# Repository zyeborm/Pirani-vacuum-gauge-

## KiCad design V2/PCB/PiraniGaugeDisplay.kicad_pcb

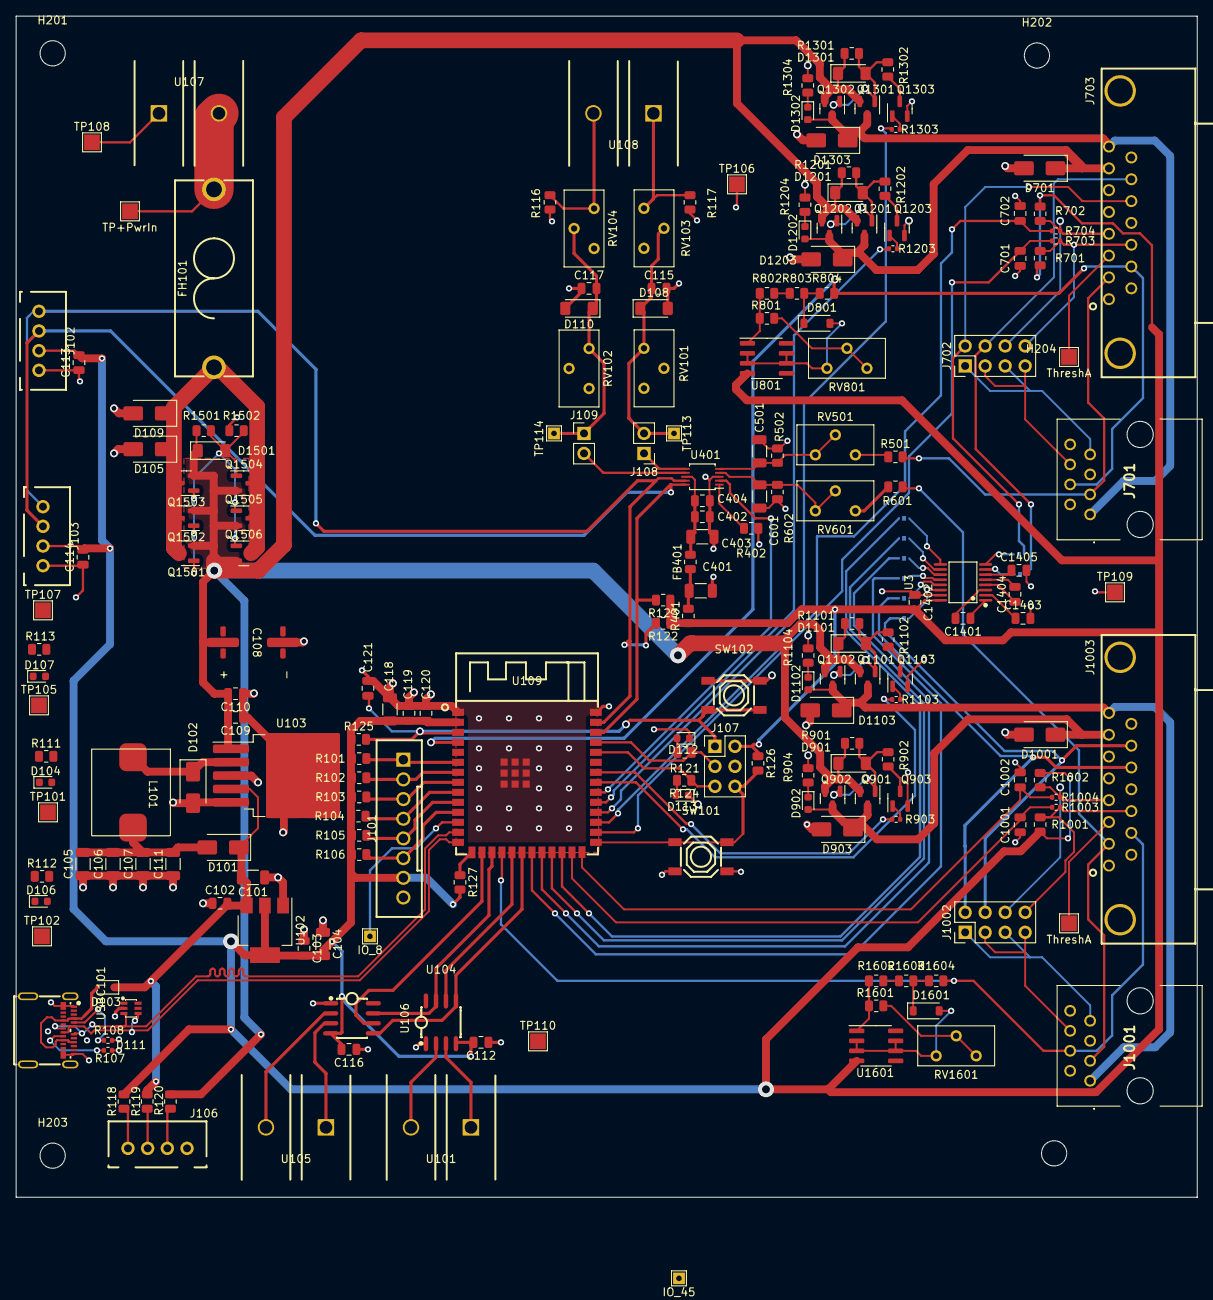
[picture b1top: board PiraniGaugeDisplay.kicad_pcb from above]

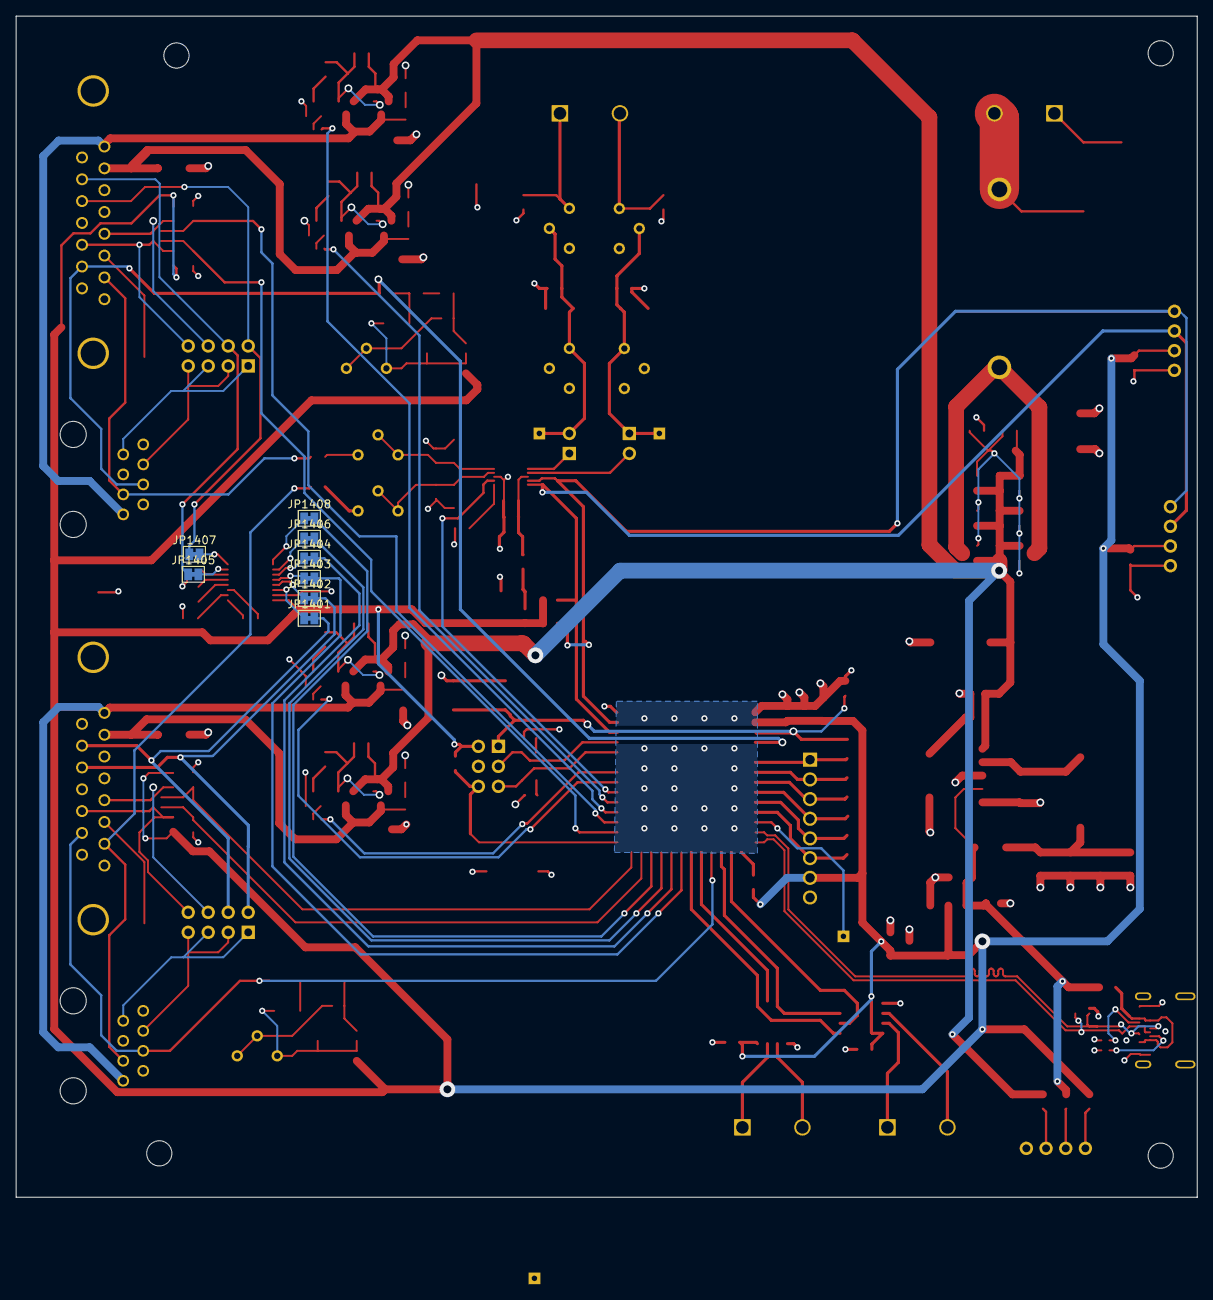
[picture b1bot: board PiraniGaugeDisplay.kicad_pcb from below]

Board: 4 copper layers, 150.0 x 150.0 mm, 214 parts (8 on the bottom side), 132 nets.

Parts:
C101, C104, C105, C106, C107, C111, C118, C402: 47uF; C_1206_3216Metric
C102, C103, C110, C112, C113, C114, C116, C120, C404, C1401, C1403, C1404, C1405: 100nf; C_0805_2012Metric
C108: 220uF; VF_C_Panasonic_ZA_SizeG_VibrationProof
C109, C115, C117, C119, C121, C403, C701, C702, C1001, C1002, C1402: 1uf; C_0805_2012Metric
C401, C501, C601: 10uF; C_1206_3216Metric
D101, D102, D109, D903, D1103, D1203, D1303: SS54; D_SMA
D103: 1N5819WS; D_SOD-323
D104, D106, D107, D112, D113, D902, D1102, D1202, D1302: LED; LED_0603_1608Metric
D105, D701, D1001: SMAJ30CA; D_SMA
D108, D110: ZMM3V3-M; D_MiniMELF
D111: SMF05CT1G; SOT-363_L2.0-W1.3-P0.65-LS2.1-BR
D801, D1601: 1N4148W; D_SOD-123
D901, D1101, D1201, D1301, D1501: ZMM5V6-M; D_MiniMELF
FB401: 300m; R_0805_2012Metric
FH101: FH1-200CK-B; FUSE-TH_L24.8-W9.8-P22.60
H201, H202, H203, H204: MountingHole; MountingHole_3.2mm_M3
J101: B8B-XH-A (LF)(SN); CONN-TH_B8B-XH-A-LF-SN
J102, J103, J106: Conn_01x04; CONN-TH_B4B-XH-A-LF-SN
J107: Conn_02x03_Odd_Even; PinHeader_2x03_P2.54mm_Vertical
J108: Aux1_Iso; PinHeader_1x02_P2.54mm_Vertical
J109: Aux2_Iso; PinHeader_1x02_P2.54mm_Vertical
J701, J1001: RJ45; 55551621
J702, J1002: Conn_02x04_Counter_Clockwise; PinHeader_2x04_P2.54mm_Vertical
J703, J1003: DA15_Plug; DSUB-TH_Z-SUBDRBM602A002
JP1401, JP1402, JP1403, JP1404, JP1405, JP1406, JP1407, JP1408: Jumper_2_Bridged; SolderJumper-2_P1.3mm_Bridged_Pad1.0x1.5mm
L101: 47uH; VF_L_MDA_1040
Q901, Q902, Q1101, Q1102, Q1201, Q1202, Q1301, Q1302, Q1501, Q1502, Q1503, Q1504, Q1505, Q1506: AO3401A; SOT-23
Q903, Q1103, Q1203, Q1303: AO3400A; SOT-23
R101, R102, R103, R104, R105, R106, R111, R112, R118, R119, R121, R122, R123, R124, R402, R701, R702, R1001, R1002: 4K7; R_0805_2012Metric
R107, R108: 5K6; R_0402_1005Metric
R113, R116, R117, R120, R125, R501, R601, R902, R904, R1102, R1104, R1202, R1204, R1302, R1304, R1502: 10K; R_0805_2012Metric
R126, R801, R1601: 3K; R_0805_2012Metric
R127: 100K; R_0805_2012Metric
R401: 10R; R_0805_2012Metric
R502, R602: 2K7; R_0805_2012Metric
R703, R704, R1003, R1004: 4k7; R_0402_1005Metric
R802, R1602: 33K; R_0805_2012Metric
R803, R1603: 1K2; R_0805_2012Metric
R804, R1604: 1K; R_0805_2012Metric
R901, R1101, R1201, R1301, R1501: 3K6; R_0805_2012Metric
R903, R1103, R1203, R1303: 1K; R_0402_1005Metric
RV101, RV102, RV103, RV104, RV501, RV601, RV801, RV1601: 1K; Potentiometer_Bourns_3296Y_Vertical
SW101, SW102: TS-1187A-B-A-B; SW-SMD_4P-L5.1-W5.1-P3.70-LS6.5-TL-2
TP101: TP+5v; TestPoint_Pad_2.0x2.0mm
TP102: TP+3.3; TestPoint_Pad_2.0x2.0mm
TP103: TP+PwrIn; TestPoint_Pad_2.0x2.0mm
TP104: IO_45; TestPoint_THTPad_1.5x1.5mm_Drill0.7mm
TP105: TP+24; TestPoint_Pad_2.0x2.0mm
TP106: TP_GND; TestPoint_Pad_2.0x2.0mm
TP107, TP108, TP109, TP110: SW_GND; TestPoint_Pad_2.0x2.0mm
TP112: IO_8; TestPoint_THTPad_1.5x1.5mm_Drill0.7mm
TP113: TP_Aux1; TestPoint_THTPad_1.5x1.5mm_Drill0.7mm
TP114: TP_Aux2; TestPoint_THTPad_1.5x1.5mm_Drill0.7mm
TP701, TP1001: ThreshA; TestPoint_Pad_2.0x2.0mm
U3: SP3232EEY-L/TR; TSSOP-16_L5.0-W4.4-P0.65-LS6.4-BL
U101, U105, U107, U108: MX25C-7.62-BK01-02P-CU-S-A; CONN-TH_2P-P7.62_MAX_MX25C-7.62-BK01-02P-CU-S-A
U102: AMS1117-3.3; SOT-223-3_TabPin2
U103: LM2596S-5; TO-263-5_TabPin3
U104, U106: MAX6675ISA+T; SOIC-8_L5.0-W4.0-P1.27-LS6.0-BL
U109: ESP32-S3-WROOM-1(N16R2); WIRELM-SMD_ESP32-S3-WROOM-1
U401: ADS1115IDGS; TSSOP-10_3x3mm_P0.5mm
U801, U1601: LM334M; SOIC-8_3.9x4.9mm_P1.27mm
USBC101: 105450-0101; USB-C-SMD_TYPE-C-USB-18

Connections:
+3.3V: C103.2, C104.2, C112.2, C113.2, C114.2, C116.2, C118.2, C119.1, C120.1, C1402.2, D106.2 (A), J101.7, J102.2, J103.2, J107.2, R101.1, R102.1, R103.1, R104.1, R105.1, R106.1, R118.1, R122.1, R123.1, R125.1, R126.1, R127.2, R401.1, R701.2, R702.1, R1001.2, R1002.1, TP102.1, U3.16 (VCC), U102.2 (VO), U104.4 (VCC), U106.4 (VCC), U109.2 (3V3), U801.4, U1601.4
+5V: C101.2, C102.2, D101.1 (K), D103.1 (K), D104.2 (A), R119.1, TP101.1, U102.3 (VI), U103.4 (FB)
+24V: C108.1, C109.2, C110.2, D107.2 (A), D901.1 (K), D1101.1 (K), D1201.1 (K), D1301.1 (K), D1501.1 (K), Q901.2 (S), Q902.2 (S), Q1101.2 (S), Q1102.2 (S), Q1201.2 (S), Q1202.2 (S), Q1301.2 (S), Q1302.2 (S), Q1501.2 (S), Q1502.2 (S), Q1503.2 (S), Q1504.2 (S), Q1505.2 (S), Q1506.2 (S), R120.2, R901.1, R1101.1, R1201.1, R1301.1, R1501.1, TP105.1, U103.1 (VIN)
/5vB4Diode: C105.2, C106.2, C107.2, C111.2, D101.2 (A), L101.2
/5vSwitchingNode: D102.1 (K), L101.1, U103.2 (OUT)
/ADC_ADS1115/3.3vADCSupply: C402.1, C403.2, C404.2, FB401.2, U401.8 (VDD)
/ADC_ADS1115/Alert: U109.32 (IO39), U401.2 (ALERT/RDY)
/ADC_ADS1115/Press0ADC_Filt: C601.1, R602.2, RV601.1, RV601.2, U401.4 (AIN0)
/ADC_ADS1115/Press1ADC_Filt: C501.1, R502.2, RV501.1, RV501.2, U401.5 (AIN1)
/Aux1_Filt: J108.1, U401.6 (AIN2)
/Aux1_Raw: R117.2, RV103.1, U108.1
/Aux2_Filt: J109.2, U401.7 (AIN3)
/Aux2_Raw: R116.2, RV104.3, U108.2
/BT1: J101.1, R101.2, U109.6 (IO6)
/BT2: J101.2, R102.2, U109.7 (IO7)
/BT3: J101.3, R103.2, U109.8 (IO15)
/BT4: J101.4, R104.2, U109.9 (IO16)
/BT5: J101.5, R105.2, U109.10 (IO17)
/BT6: J101.6, R106.2, U109.11 (IO18)
/DualExternalConnector1/Degas: D701.1 (A1), D1202.2 (A), D1203.1 (K), J703.7, Q1201.3 (D), Q1202.3 (D)
/DualExternalConnector1/Filament_Status/SP2: C701.2, R703.2, U109.28 (IO35)
/DualExternalConnector1/Identification: J701.4, J703.10, R804.1, U109.4 (IO4)
/DualExternalConnector1/PowerIn: D1302.2 (A), D1303.1 (K), J701.1, J703.8, Q1301.3 (D), Q1302.3 (D)
/DualExternalConnector1/RS232_Rx: J702.4, J703.14, JP1405.1 (A)
/DualExternalConnector1/RS232_Tx: J702.2, J703.13, JP1407.1 (A)
/DualExternalConnector1/Raw_Analog_Measurement: J701.3, J703.2, R501.2
/DualExternalConnector1/Relay_Filament_Status: J702.8, J703.11 (P111), R701.1, R703.1
/DualExternalConnector1/Relay_SP: J702.6, J703.4, R702.2, R704.1
/DualExternalConnector1/Relay_SP1 | Rs232Tx: J701.7, J702.1, J702.5
/DualExternalConnector1/Relay_SP2 | Rs232Rx: J701.6, J702.3, J702.7
/DualExternalConnector1/SP1: C702.2, R704.2, U109.29 (IO36)
/DualExternalConnector1/Thresh_A: J703.3, TP701.1
/DualExternalConnector/Degas: D902.2 (A), D903.1 (K), D1001.1 (A1), J1003.7, Q901.3 (D), Q902.3 (D)
/DualExternalConnector/Identification: J1001.4, J1003.10, R1604.1, U109.18 (IO10)
/DualExternalConnector/PowerIn: D1102.2 (A), D1103.1 (K), J1001.1, J1003.8, Q1101.3 (D), Q1102.3 (D)
/DualExternalConnector/Raw_Analog_Measurement: J1001.3, J1003.2, R601.2
/DualExternalConnector/Relay_Filament_Status: J1002.8, J1003.11 (P111), R1001.1, R1003.1
/DualExternalConnector/Relay_SP: J1002.6, J1003.4, R1002.2, R1004.1
/DualExternalConnector/Relay_SP1 | Rs232Tx: J1001.7, J1002.1, J1002.5
/DualExternalConnector/Relay_SP2 | Rs232Rx: J1001.6, J1002.3, J1002.7
/DualExternalConnector/Thresh_A: J1003.3, TP1001.1
/EC1_SP1: C1002.2, R1004.2, U109.26 (IO45)
/EC1_SP2: C1001.2, R1003.2, U109.25 (IO48)
/ESP_EN: C121.2, J107.1, R125.2, SW102.3 (C), SW102.4 (D), U109.3 (EN)
/ESP_IO0: J107.6, R126.2, SW101.1 (A), SW101.2 (B), U109.27 (IO0)
/ESP_RXD: J107.5, R124.1, U109.36 (RXD0)
/ESP_TXD: J107.3, R121.1, U109.37 (TXD0)
/HighSideDriver1/Drv_In: R1303.2, U109.30 (IO37)
/HighSideDriver2/Drv_In: R1103.2, U109.33 (IO40)
/HighSideDriver3/Drv_In: R903.2, U109.34 (IO41)
/HighSideDriver/Drv_In: R1203.2, U109.31 (IO38)
/I2C_SCL: J102.3, J103.3, R123.2, U109.38 (IO2), U401.10 (SCL)
/I2C_SDA: J102.4, J103.4, R122.2, U109.39 (IO1), U401.9 (SDA)
/IdealishDiode/Din: D105.1 (A1), D109.1 (K), FH101.1, Q1501.3 (D), Q1502.3 (D), Q1503.3 (D), Q1504.3 (D), Q1505.3 (D), Q1506.3 (D)
/K_CS1: U104.6 (~CS), U109.19 (IO11)
/K_CS2: U106.6 (~CS), U109.16 (IO46)
/PwrIn: FH101.2, TP103.1, U107.2
/RS232 - TTL/Rx_D1: JP1403.2 (B), U109.21 (IO13)
/RS232 - TTL/Rx_D2: JP1408.2 (B), U109.24 (IO47)
/RS232 - TTL/Tx_D1: JP1404.2 (B), U109.22 (IO14)
/RS232 - TTL/Tx_D2: JP1406.2 (B), U109.23 (IO21)
/Rx_D_R1: J1002.2, J1003.13, JP1402.2 (B)
/SPI_SCK: U104.5 (SCK), U106.5 (SCK), U109.20 (IO12)
/SPI_SDO: U104.7 (SO), U106.7 (SO), U109.17 (IO9)
/Tx_D_R1: J1002.4, J1003.14, JP1401.2 (B)
/USB_D+: D111.4, U109.14 (IO20), USBC101.A6 (D+), USBC101.B6 (D+)
/USB_D-: D111.3, U109.13 (IO19), USBC101.A7 (D-), USBC101.B7 (D-)
GND: C101.1, C102.1, C103.1, C104.1, C105.1, C106.1, C107.1, C108.2, C109.1, C110.1, C111.1, C112.1, C113.1, C114.1, C115.2, C116.1, C117.1, C118.1, C119.2, C120.2, C121.1, C401.2, C402.2, C403.1, C404.1, C501.2, C601.2, C701.1, C702.1, C1001.1, C1002.1, C1402.1, C1403.2, C1405.2, D102.2 (A), D105.2 (A2), D108.2 (A), D109.2 (A), D110.2 (A), D111.2, D112.1 (K), D113.1 (K), D701.2 (A2), D903.2 (A), D1001.2 (A2), D1103.2 (A), D1203.2 (A), D1303.2 (A), J101.8, J102.1, J103.1, J106.1, J107.4, J701.2, J701.5, J701.8, J703.0 (PAD), J703.1, J703.5, J703.9, J703.12, J1001.2, J1001.5, J1001.8, J1003.0 (PAD), J1003.1, J1003.5, J1003.9, J1003.12, Q903.2 (S), Q1103.2 (S), Q1203.2 (S), Q1303.2 (S), R107.2, R108.1, R111.2, R112.2, R113.1, R116.1, R117.1, R402.2, R502.1, R602.1, R904.1, R1104.1, R1204.1, R1304.1, R1502.1, RV101.2, RV102.2, SW101.3 (C), SW101.4 (D), SW102.1 (A), SW102.2 (B), TP106.1, TP107.1, TP108.1, TP109.1, TP110.1, U3.15 (GND), U102.1 (GND), U103.3 (GND), U103.5 (~ON/OFF), U104.1 (GND), U106.1 (GND), U107.1, U109.1 (GND), U109.40 (GND), U109.41 (GND), U401.3 (GND), USBC101.A1 (GND), USBC101.A12 (GND), USBC101.B1 (GND), USBC101.B12 (GND)
unnamed: C401.1, FB401.1, R401.2
unnamed: D103.2 (A), USBC101.A4 (VBUS), USBC101.A9 (VBUS), USBC101.B4 (VBUS), USBC101.B9 (VBUS)
unnamed: D104.1 (K), R111.1
unnamed: D106.1 (K), R112.1
unnamed: D107.1 (K), R113.2
unnamed: C115.1, D108.1 (K), J108.2, RV101.1, RV103.2, TP113.1
unnamed: C117.2, D110.1 (K), J109.1, RV102.3, RV104.2, TP114.1
unnamed: D112.2 (A), R121.2
unnamed: D113.2 (A), R124.2
unnamed: D801.2 (A), RV801.1, U801.2, U801.3, U801.6, U801.7
unnamed: D801.1 (K), R803.1, R804.2
unnamed: D901.2 (A), Q901.1 (G), Q902.1 (G), R901.2, R902.2
unnamed: D902.1 (K), R904.2
unnamed: D1101.2 (A), Q1101.1 (G), Q1102.1 (G), R1101.2, R1102.2
unnamed: D1102.1 (K), R1104.2
unnamed: D1201.2 (A), Q1201.1 (G), Q1202.1 (G), R1201.2, R1202.2
unnamed: D1202.1 (K), R1204.2
unnamed: D1301.2 (A), Q1301.1 (G), Q1302.1 (G), R1301.2, R1302.2
unnamed: D1302.1 (K), R1304.2
unnamed: D1501.2 (A), Q1501.1 (G), Q1502.1 (G), Q1503.1 (G), Q1504.1 (G), Q1505.1 (G), Q1506.1 (G), R1501.2, R1502.2
unnamed: D1601.2 (A), RV1601.1, U1601.2, U1601.3, U1601.6, U1601.7
unnamed: D1601.1 (K), R1603.1, R1604.2
unnamed: J106.2, R120.1
unnamed: J106.3, R119.2
unnamed: J106.4, R118.2
unnamed: JP1401.1 (A), U3.14 (T1OUT)
unnamed: JP1402.1 (A), U3.13 (R1IN)
unnamed: JP1403.1 (A), U3.12 (R1OUT)
unnamed: JP1404.1 (A), U3.11 (T1IN)
unnamed: JP1405.2 (B), U3.7 (T2OUT)
unnamed: JP1406.1 (A), U3.10 (T2IN)
unnamed: JP1407.2 (B), U3.8 (R2IN)
unnamed: JP1408.1 (A), U3.9 (R2OUT)
unnamed: Q903.3 (D), R902.1
unnamed: Q903.1 (G), R903.1
unnamed: Q1103.3 (D), R1102.1
unnamed: Q1103.1 (G), R1103.1
unnamed: Q1203.3 (D), R1202.1
unnamed: Q1203.1 (G), R1203.1
unnamed: Q1303.3 (D), R1302.1
unnamed: Q1303.1 (G), R1303.1
unnamed: R501.1, RV501.3
unnamed: R601.1, RV601.3
unnamed: R801.1, RV801.2, RV801.3
unnamed: R801.2, R802.2, U801.1
unnamed: R802.1, R803.2
unnamed: R1601.1, RV1601.2, RV1601.3
unnamed: R1601.2, R1602.2, U1601.1
unnamed: R1602.1, R1603.2
unnamed: C1401.1, U3.1 (C1+)
unnamed: C1401.2, U3.3 (C1-)
unnamed: C1404.1, U3.4 (C2+)
unnamed: C1404.2, U3.5 (C2-)
unnamed: C1403.1, U3.2 (V+)
unnamed: C1405.1, U3.6 (V-)
unnamed: U101.1, U104.3 (T+)
unnamed: U101.2, U104.2 (T-)
unnamed: U105.1, U106.3 (T+)
unnamed: U105.2, U106.2 (T-)
unnamed: R127.1, U109.15 (IO3)
unnamed: TP112.1, U109.12 (IO8)
unnamed: R402.1, U401.1 (ADDR)
unnamed: R108.2, USBC101.A5 (CC1)
unnamed: R107.1, USBC101.B5 (CC2)

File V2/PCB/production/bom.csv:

Designator,Footprint,Quantity,Value,LCSC Part #
"C1001, C1002, C109, C115, C117, C119, C121, C1402, C403, C701, C702",0805,11,1uf,Basic Part
"C101, C104, C105, C106, C107, C111, C118, C402",1206,8,47uF,C96123
"C102, C103, C110, C112, C113, C114, C116, C120, C1401, C1403, C1404, C1405, C404",0805,13,100nf,C28233
C108,VF_C_Panasonic_ZA_SizeG_VibrationProof,1,220uF,C454357
"C401, C501, C601",1206,3,10uF,C13585
"D1001, D105, D701",D_SMA,3,SMAJ30CA,C83322
"D101, D102, D109, D1103, D1203, D1303, D903",D_SMA,7,SS54,C22452
D103,D_SOD-323,1,1N5819WS,C191023
"D104, D106, D107, D1102, D112, D113, D1202, D1302, D902",0603,9,LED,C72043
"D108, D110",D_MiniMELF,2,ZMM3V3-M,C8056
"D1101, D1201, D1301, D1501, D901",D_MiniMELF,5,ZMM5V6-M,C8062
D111,SOT-363_L2.0-W1.3-P0.65-LS2.1-BR,1,SMF05CT1G,C15879
"D1601, D801",D_SOD-123,2,1N4148W,
FB401,0805,1,300m,C1017
FH101,FUSE-TH_L24.8-W9.8-P22.60,1,FH1-200CK-B,C268205
"H201, H202, H203, H204",MountingHole_3.2mm_M3,4,MountingHole,
"J1001, J701",55551621,2,RJ45,C305976
"J1002, J702",PinHeader_2x04_P2.54mm_Vertical,2,Conn_02x04_Counter_Clockwise,
"J1003, J703",DSUB-TH_Z-SUBDRBM602A002,2,DA15_Plug,C235810
J101,CONN-TH_B8B-XH-A-LF-SN,1,B8B-XH-A (LF)(SN),C157972
"J102, J103, J106",CONN-TH_B4B-XH-A-LF-SN,3,Conn_01x04,C144395
J107,PinHeader_2x03_P2.54mm_Vertical,1,Conn_02x03_Odd_Even,C492420
J108,PinHeader_1x02_P2.54mm_Vertical,1,Aux1_Iso,
J109,PinHeader_1x02_P2.54mm_Vertical,1,Aux2_Iso,
"JP1401, JP1402, JP1403, JP1404, JP1405, JP1406, JP1407, JP1408",SolderJumper-2_P1.3mm_Bridged_Pad1.0x1.5mm,8,Jumper_2_Bridged,
L101,VF_L_MDA_1040,1,47uH,C2847557
"Q1101, Q1102, Q1201, Q1202, Q1301, Q1302, Q1501, Q1502, Q1503, Q1504, Q1505, Q1506, Q901, Q902",SOT-23,14,AO3401A,C15127
"Q1103, Q1203, Q1303, Q903",SOT-23,4,AO3400A,C20917
"R1001, R1002, R101, R102, R103, R104, R105, R106, R111, R112, R118, R119, R121, R122, R123, R124, R402, R701, R702",0805,19,4K7,C17673
"R1003, R1004, R703, R704",0402,4,4k7,C25900
"R107, R108",0402,2,5K6,C25908
"R1101, R1201, R1301, R1501, R901",0805,5,3K6,C18359
"R1102, R1104, R113, R116, R117, R120, R1202, R1204, R125, R1302, R1304, R1502, R501, R601, R902, R904",0805,16,10K,C17414
"R1103, R1203, R1303, R903",0402,4,1K,C11702
"R126, R1601, R801",0805,3,3K,C17661
R127,0805,1,100K,C149504
"R1602, R802",0805,2,33K,C17633
"R1603, R803",0805,2,1K2,C17379
"R1604, R804",0805,2,1K,C17379
R401,0805,1,10R,C17415
"R502, R602",0805,2,2K7,C17530
"RV101, RV102, RV103, RV104, RV1601, RV501, RV601, RV801",Potentiometer_Bourns_3296Y_Vertical,8,1K,C83688
"SW101, SW102",SW-SMD_4P-L5.1-W5.1-P3.70-LS6.5-TL-2,2,TS-1187A-B-A-B,C318884
"TP1001, TP701",TestPoint_Pad_2.0x2.0mm,2,ThreshA,
TP101,TestPoint_Pad_2.0x2.0mm,1,TP+5v,
TP102,TestPoint_Pad_2.0x2.0mm,1,TP+3.3,
TP103,TestPoint_Pad_2.0x2.0mm,1,TP+PwrIn,
TP104,TestPoint_THTPad_1.5x1.5mm_Drill0.7mm,1,IO_45,
TP105,TestPoint_Pad_2.0x2.0mm,1,TP+24,
TP106,TestPoint_Pad_2.0x2.0mm,1,TP_GND,
"TP107, TP108, TP109, TP110",TestPoint_Pad_2.0x2.0mm,4,SW_GND,
TP112,TestPoint_THTPad_1.5x1.5mm_Drill0.7mm,1,IO_8,
TP113,TestPoint_THTPad_1.5x1.5mm_Drill0.7mm,1,TP_Aux1,
TP114,TestPoint_THTPad_1.5x1.5mm_Drill0.7mm,1,TP_Aux2,
"U101, U105, U107, U108",CONN-TH_2P-P7.62_MAX_MX25C-7.62-BK01-02P-CU-S-A,4,MX25C-7.62-BK01-02P-CU-S-A,C5188509
U102,SOT-223-3_TabPin2,1,AMS1117-3.3,C6186
U103,TO-263-5_TabPin3,1,LM2596S-5,
"U104, U106",SOIC-8_L5.0-W4.0-P1.27-LS6.0-BL,2,MAX6675ISA+T,C16030
U109,WIRELM-SMD_ESP32-S3-WROOM-1,1,ESP32-S3-WROOM-1(N16R2),C2913205
"U1601, U801",SOIC-8_3.9x4.9mm_P1.27mm,2,LM334M,
U3,TSSOP-16_L5.0-W4.4-P0.65-LS6.4-BL,1,SP3232EEY-L/TR,C13482
U401,TSSOP-10_3x3mm_P0.5mm,1,ADS1115IDGS,
USBC101,USB-C-SMD_TYPE-C-USB-18,1,105450-0101,C134092

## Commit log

2023-11-22 Prep for V2
    Created V1 folder put old version there.
    Created V2 folder and put new schematic in that
    Copied schematic symbols to project specific library
2023-11-22 Added buttons
    Added boot/reset buttons to PCB
    Should probably add some extras just for future expansion
2023-11-23 Added ADC
2023-11-23 Dumped parts onto PCB and made project library
    This should get the footprints moved over.
    I'll look to move the 3d models over next.
2023-11-23 saved PCB
2023-11-23 Added 3d models to local library
2023-11-25 Changed ADC divider
    Changed ADC divider to give 1.9v for 10V in this matches up with the 2.048v input range on the ADC
2024-01-30 added double plug
2024-01-31 added thermocouple
2024-02-11 Schematic "Finished"
2024-02-13 PCB layout first pass
2024-02-18 pre-discussion
    fin
